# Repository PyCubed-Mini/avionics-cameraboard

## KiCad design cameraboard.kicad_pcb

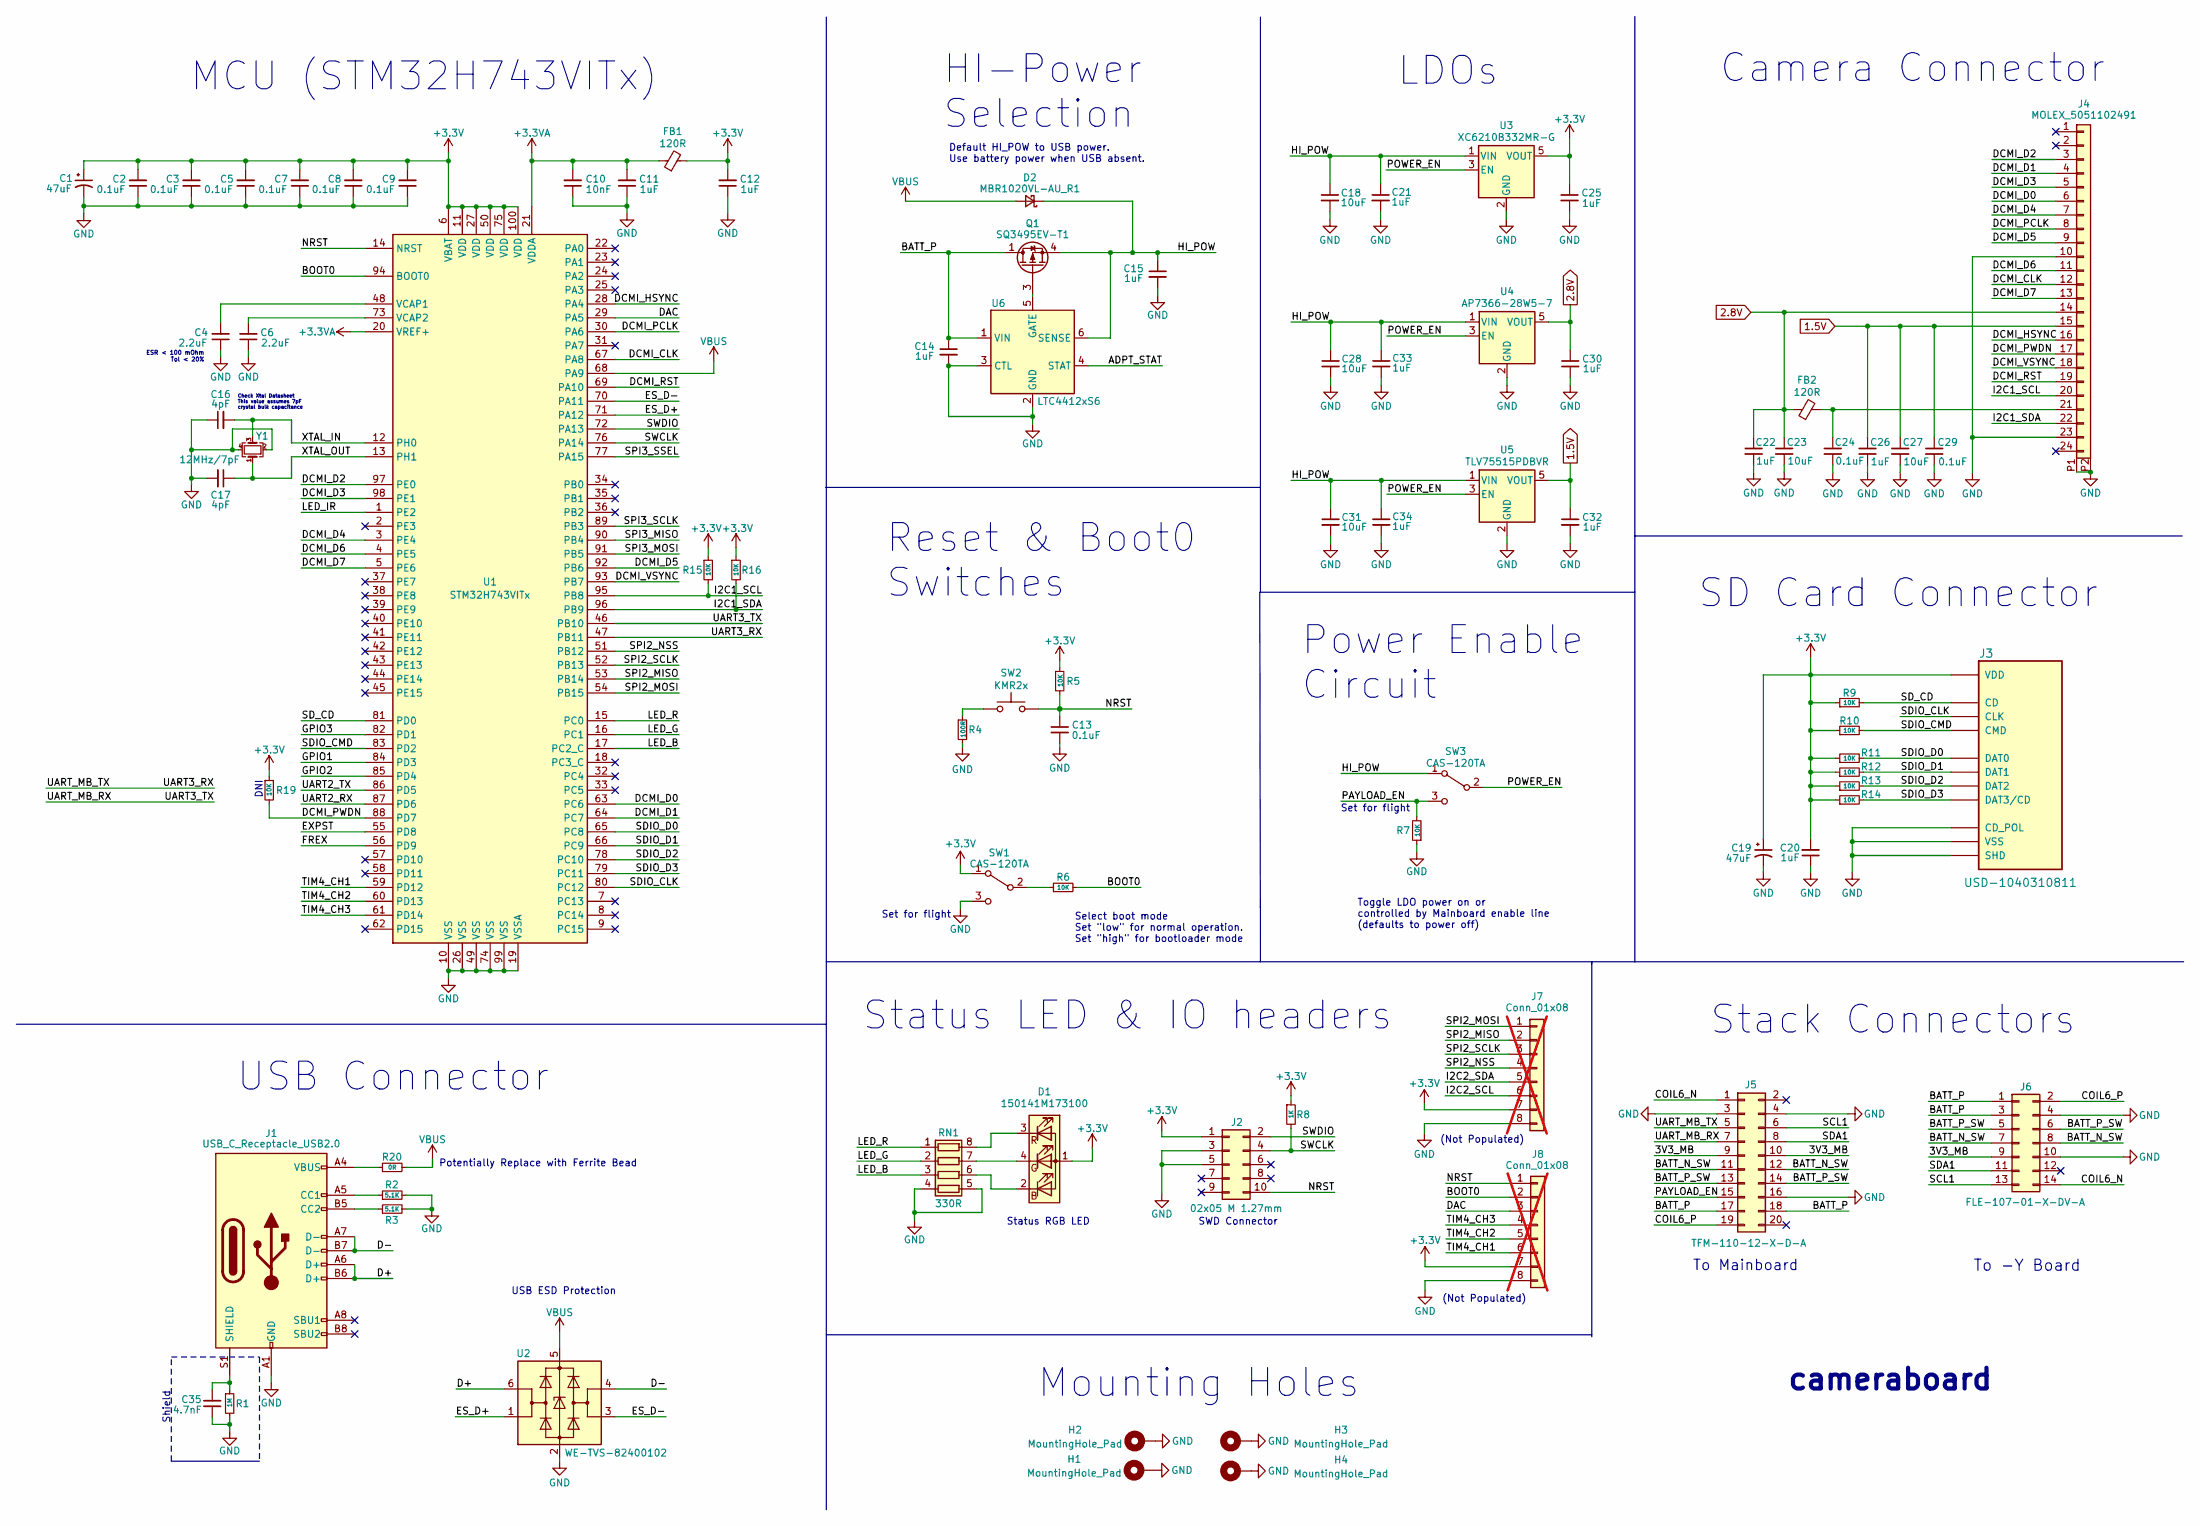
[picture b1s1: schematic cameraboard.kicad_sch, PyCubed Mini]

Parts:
C1, C19: 47uF; CP_EIA-2012-12_Kemet-R
C2, C3, C5, C7, C8, C9, C13, C24, C29: 0.1uF; C_0603_1608Metric
C4, C6: 2.2uF; C_0603_1608Metric
C10: 10nF; C_0603_1608Metric
C11, C12, C14, C15, C20, C21, C22, C25, C26, C30, C32, C33, C34: 1uF; C_0603_1608Metric
C16, C17: 4pF; C_0603_1608Metric
C18, C23, C27, C28, C31: 10uF; C_0603_1608Metric
C35: 4.7nF; C_0603_1608Metric
D1: 150141M173100; LED_RGB_Wuerth-PLCC4_3.2x2.8mm_150141M173100
D2: MBR1020VL-AU_R1; D_SOD-123F
FB1, FB2: 120R; L_0603_1608Metric
H1, H2, H3, H4: MountingHole_Pad; MountingHole
J1: USB_C_Receptacle_USB2.0; USB_C_Receptacle_HRO_TYPE-C-31-M-12
J2: 02x05 M 1.27mm; PinHeader_2x05_P1.27mm_Vertical_SMD
J3: USD-1040310811; microSD_HC_Molex_104031-0811
J4: MOLEX_5051102491
J5: TFM-110-12-X-D-A; SAMTEC_TFM-110-12-X-D-A
J6: FLE-107-01-X-DV-A; SAMTEC_FLE-107-01-X-DV-A
J7, J8: Conn_01x08; PinHeader_1x08_P2.54mm_Vertical; not fitted
Q1: SQ3495EV-T1; SOT-23-6
R1: 1M; R_0603_1608Metric
R2, R3: 5.1K; R_0603_1608Metric
R4: 100R; R_0603_1608Metric
R5, R6, R7, R9, R10, R11, R12, R13, R14, R15, R16, R19: 10K; R_0603_1608Metric
R8: 1K; R_0603_1608Metric
R20: 0R; R_0603_1608Metric
RN1: 330R; R_Array_Concave_4x0603
SW1, SW3: CAS-120TA
SW2: KMR2x; BTN_KMR2
U1: STM32H743VITx; LQFP-100_14x14mm_P0.5mm
U2: WE-TVS-82400102; SOT-23-6
U3: XC6210B332MR-G; SOT-23-5
U4: AP7366-28W5-7; SOT-23-5
U5: TLV75515PDBVR; SOT-23-5
U6: LTC4412xS6; TSOT-23-6
Y1: 12MHz/7pF; Crystal_SMD_2520-4Pin_2.5x2.0mm

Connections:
1.5V: C26.1, C27.1, C29.1, C32.1, J4.15, U5.5 (VOUT)
2.8V: C22.1, C23.1, C30.1, FB2.1, J4.14, U4.5 (VOUT)
+3.3V: C1.1, C2.2, C3.2, C5.2, C7.2, C8.2, C9.2, C12.2, C19.1, C20.2, C25.1, D1.1 (A), FB1.2, J2.1, J3.4 (VDD), J7.7, J8.7, R5.1, R8.1, R9.1, R10.1, R11.1, R12.1, R13.1, R14.1, R15.1, R16.1, R19.1, SW1.1 (A), U1.6 (VBAT), U1.11 (VDD), U1.27 (VDD), U1.50 (VDD), U1.75 (VDD), U1.100 (VDD), U3.5 (VOUT)
+3.3VA: C10.2, C11.2, FB1.1, U1.20 (VREF+), U1.21 (VDDA)
/3V3_MB: J5.9, J5.10, J6.9
/ADPT_STAT: U6.4 (STAT)
/BATT_N_SW: J5.11, J5.12, J6.7, J6.8
/BATT_P: C14.1, J5.17, J5.18, J6.1, J6.3, Q1.1 (D), Q1.2 (D), Q1.5 (D), Q1.6 (D), U6.1 (VIN)
/BATT_P_SW: J5.13, J5.14, J6.5, J6.6
/BOOT0: J8.2, R6.2, U1.94 (BOOT0)
/COIL6_N: J5.1, J6.14
/COIL6_P: J5.19, J6.2
/D+: J1.A6 (D+), J1.B6 (D+), U2.6 (I/O1)
/D-: J1.A7 (D-), J1.B7 (D-), U2.4 (I/O2)
/DAC: J8.3, U1.29 (PA5)
/DCMI_CLK: J4.12, U1.67 (PA8)
/DCMI_D0: J4.6, U1.63 (PC6)
/DCMI_D1: J4.4, U1.64 (PC7)
/DCMI_D2: J4.3, U1.97 (PE0)
/DCMI_D3: J4.5, U1.98 (PE1)
/DCMI_D4: J4.7, U1.3 (PE4)
/DCMI_D5: J4.9, U1.92 (PB6)
/DCMI_D6: J4.11, U1.4 (PE5)
/DCMI_D7: J4.13, U1.5 (PE6)
/DCMI_HSYNC: J4.16, U1.28 (PA4)
/DCMI_PCLK: J4.8, U1.30 (PA6)
/DCMI_PWDN: J4.17, R19.2, U1.88 (PD7)
/DCMI_RST: J4.19, U1.69 (PA10)
/DCMI_VSYNC: J4.18, U1.93 (PB7)
/ES_D+: U1.71 (PA12), U2.1 (I/O1)
/ES_D-: U1.70 (PA11), U2.3 (I/O2)
/EXPST: U1.55 (PD8)
/FREX: U1.56 (PD9)
/GPIO1: U1.84 (PD3)
/GPIO2: U1.85 (PD4)
/GPIO3: U1.82 (PD1)
/HI_POW: C15.1, C18.1, C21.1, C28.1, C31.1, C33.1, C34.1, D2.1 (K), Q1.4 (S), SW3.1 (A), U3.1 (VIN), U4.1 (VIN), U5.1 (VIN), U6.6 (SENSE)
/I2C1_SCL: J4.20, R15.2, U1.95 (PB8)
/I2C1_SDA: J4.22, R16.2, U1.96 (PB9)
/LED_B: RN1.3 (R3.1), U1.17 (PC2_C)
/LED_G: RN1.2 (R2.1), U1.16 (PC1)
/LED_IR: U1.1 (PE2)
/LED_R: RN1.1 (R1.1), U1.15 (PC0)
/NRST: C13.1, J2.10, J8.1, R5.2, SW2.2, U1.14 (NRST)
/PAYLOAD_EN: J5.15, R7.2, SW3.3 (C)
/POWER_EN: SW3.2 (B), U3.3 (EN), U4.3 (EN), U5.3 (EN)
/SCL1: J5.6, J6.13
/SDA1: J5.8, J6.11
/SDIO_CLK: J3.5 (CLK), U1.80 (PC12)
/SDIO_CMD: J3.3 (CMD), R10.2, U1.83 (PD2)
/SDIO_D0: J3.7 (DAT0), R11.2, U1.65 (PC8)
/SDIO_D1: J3.8 (DAT1), R12.2, U1.66 (PC9)
/SDIO_D2: J3.1 (DAT2), R13.2, U1.78 (PC10)
/SDIO_D3: J3.2 (DAT3/CD), R14.2, U1.79 (PC11)
/SD_CD: J3.10 (CD), R9.2, U1.81 (PD0)
/SPI2_MISO: J7.2, U1.53 (PB14)
/SPI2_MOSI: J7.1, U1.54 (PB15)
/SPI2_NSS: J7.4, U1.51 (PB12)
/SPI2_SCLK: J7.3, U1.52 (PB13)
/SPI3_MISO: U1.90 (PB4)
/SPI3_MOSI: U1.91 (PB5)
/SPI3_SCLK: U1.89 (PB3)
/SPI3_SSEL: U1.77 (PA15)
/SWCLK: J2.4, R8.2, U1.76 (PA14)
/SWDIO: J2.2, U1.72 (PA13)
/TIM4_CH1: J8.6, U1.59 (PD12)
/TIM4_CH2: J8.5, U1.60 (PD13)
/TIM4_CH3: J8.4, U1.61 (PD14)
/UART2_RX: U1.87 (PD6)
/UART2_TX: U1.86 (PD5)
/UART3_RX: J5.5, U1.47 (PB11)
/UART3_TX: J5.7, U1.46 (PB10)
/XTAL_IN: C16.2, U1.12 (PH0), Y1.3
/XTAL_OUT: C17.1, U1.13 (PH1), Y1.1
GND: C1.2, C2.1, C3.1, C4.1, C5.1, C6.1, C7.1, C8.1, C9.1, C10.1, C11.1, C12.1, C13.2, C14.2, C15.2, C16.1, C17.2, C18.2, C19.2, C20.1, C21.2, C22.2, C23.2, C24.2, C25.2, C26.2, C27.2, C28.2, C29.2, C30.2, C31.2, C32.2, C33.2, C34.2, C35.1, H1.1, H2.1, H3.1, H4.1, J1.A1 (GND), J1.A12 (GND), J1.B1 (GND), J1.B12 (GND), J2.3, J2.5, J3.6 (VSS), J3.9 (CD_POL), J3.11 (SHD), J4.10, J4.23, J4.P1, J4.P2, J5.3, J5.4, J5.16, J6.4, J6.10, J7.8, J8.8, R1.2, R2.2, R3.2, R4.2, R7.1, RN1.4 (R4.1), RN1.5 (R4.2), SW1.3 (C), U1.10 (VSS), U1.19 (VSSA), U1.26 (VSS), U1.49 (VSS), U1.74 (VSS), U1.99 (VSS), U2.2 (GND), U3.2 (GND), U4.2 (GND), U5.2 (GND), U6.2 (GND), U6.3 (CTL), Y1.2, Y1.4
unnamed: D1.2 (BK), RN1.6 (R3.2)
unnamed: D1.4 (GK), RN1.7 (R2.2)
unnamed: D1.3 (RK), RN1.8 (R1.2)
unnamed: J1.A5 (CC1), R2.1
unnamed: J1.B5 (CC2), R3.1
unnamed: C35.2, J1.S1 (SHIELD), R1.1
unnamed: J1.A4 (VBUS), J1.A9 (VBUS), J1.B4 (VBUS), J1.B9 (VBUS), R20.1
unnamed: C24.1, FB2.2, J4.21
unnamed: Q1.3 (G), U6.5 (GATE)
unnamed: R4.1, SW2.1
unnamed: R6.1, SW1.2 (B)
unnamed: C4.2, U1.48 (VCAP1)
unnamed: C6.2, U1.73 (VCAP2)
VBUS: D2.2 (A), R20.2, U1.68 (PA9), U2.5 (VBUS)

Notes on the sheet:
Mounting Holes
Set for flight
cameraboard
SD Card Connector
(Not Populated)
Check Xtal Datasheet This value assumes 7pF crystal bulk capacitance
Power Enable Circuit
HI-Power Selection
To Mainboard
To -Y Board
Potentially Replace with Ferrite Bead
Status LED & IO headers
DNI
MCU (STM32H743VITx)
Status RGB LED
SWD Connector
Reset & Boot0 Switches
Stack Connectors
Toggle LDO power on or controlled by Mainboard enable line (defaults to power off)
Shield
LDOs
Select boot mode Set "low" for normal operation. Set "high" for bootloader mode
USB Connector
Camera Connector
ESR < 100 mOhm Tol < 20%
Default HI_POW to USB power. Use battery power when USB absent.
USB ESD Protection

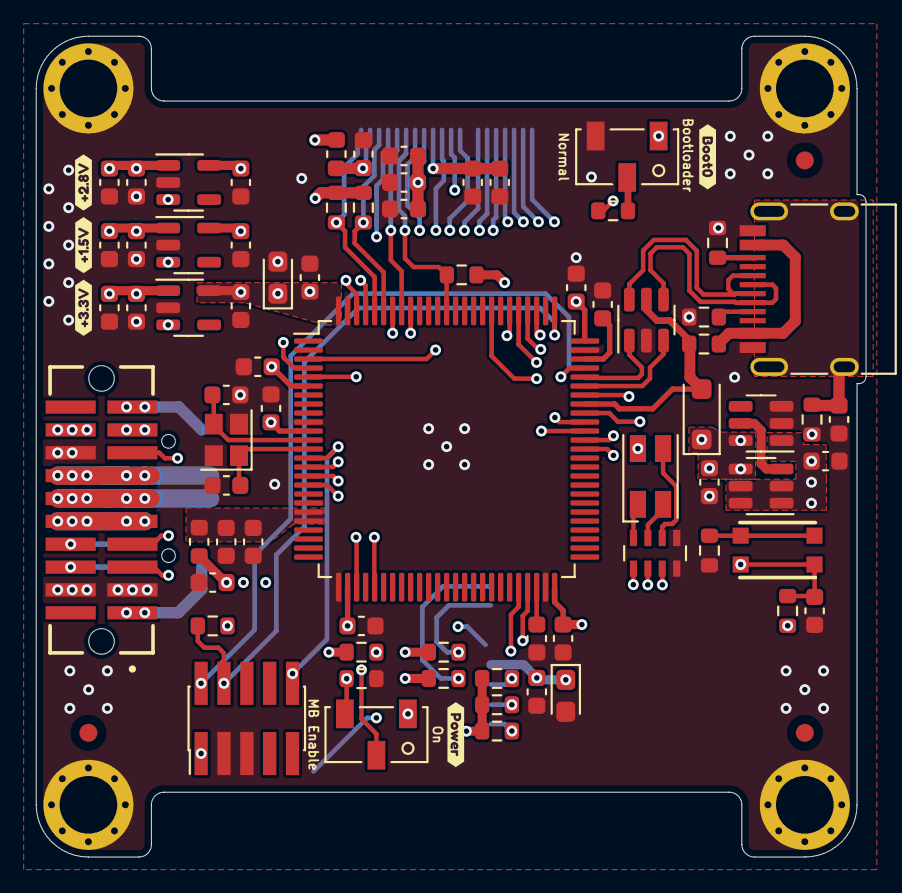
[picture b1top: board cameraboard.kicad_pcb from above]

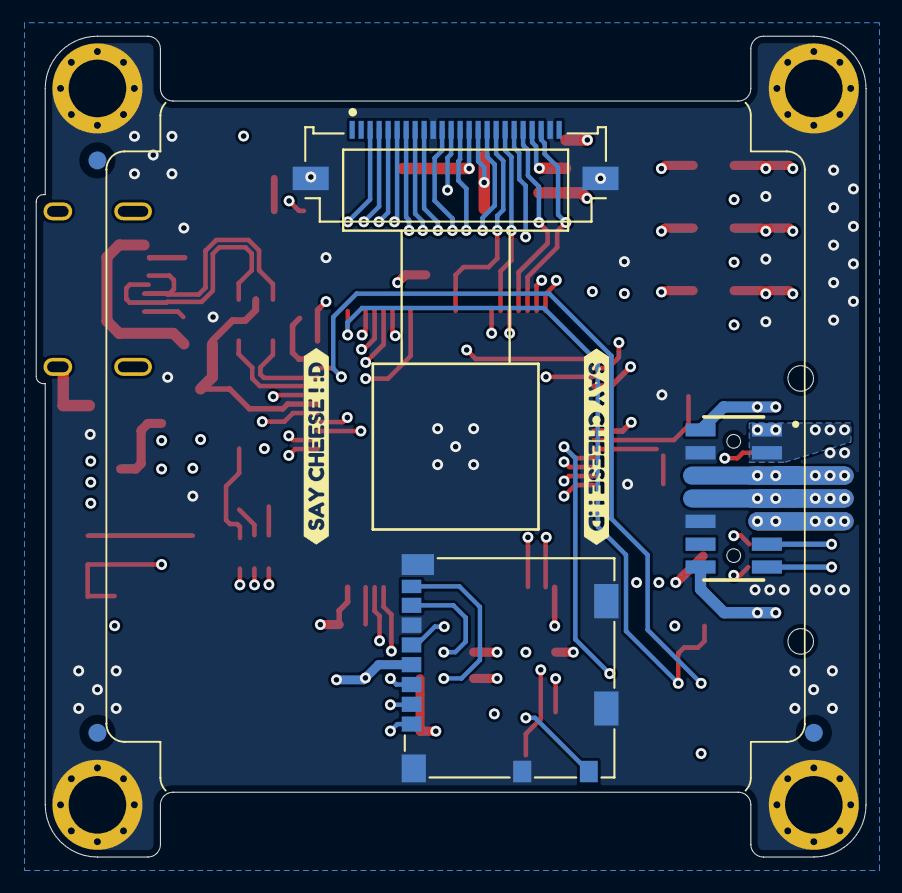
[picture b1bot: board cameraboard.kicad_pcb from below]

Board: 4 copper layers, 46.1 x 45.6 mm, 87 parts (5 on the bottom side), 68 nets.

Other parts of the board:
Ref**: Val**; pycubed_mini_half
kibuzzard-63E3EA3E: G***; kibuzzard-63E3EA3E
kibuzzard-63E3EAF3: G***; kibuzzard-63E3EAF3
kibuzzard-63E3EBF1: G***; kibuzzard-63E3EBF1
kibuzzard-63E3EC1C: G***; kibuzzard-63E3EC1C
kibuzzard-63E3EC09: G***; kibuzzard-63E3EC09
kibuzzard-63E3ED57, kibuzzard-63E3ED57#2: G***; kibuzzard-63E3ED57

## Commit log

2022-03-24 File upload
2022-03-24 camera step file
2022-03-24 black gloss
2022-03-24 Updated PCB 3d model
2022-03-25 Moved nicla model to kicad_libs, exported pcb model
2022-03-28 Added Mounting Holes on main and camera boards
2022-05-31 Changed board shape and rewired
2022-06-02 Schematic fixes and re-routing
2022-06-03 Moved stuff into place
2022-06-08 stack connectors changes
2022-06-09 VBUS -> VUSB
2022-06-09 Moved connectors as recommended
2022-06-09 Rename VBUS to VUSB and export files
2022-06-09 Added Logo, version number and date
2022-06-10 Exported Gerbers
2022-06-27 Moved Camera slightly, added bus protection
2022-06-29 moved camera connector
2022-06-29 moved connector
2022-06-29 Re-routed for new connector location
2022-06-29 Re-check board and re-export model
2022-06-30 new outline of camera board
2022-07-01 New cameraboard outline
2022-07-06 nikla -> nicla
2022-07-06 Export New Gerbers
2022-08-24 Custom spun board updates
2022-12-23 Change Stash
2023-02-08 Finished Routing
2023-02-09 Export 3D Model
2023-02-19 Simplified Enable Circuit
2023-02-22 Stash before changes
2023-02-25 Moved SWD header and power switch to prevent mechanical interference
2023-02-25 Pulled latest kicad-libs
2023-02-26 Removed gerbers from repo
2023-04-27 Rev B3/02 updates
2023-06-18 Rewired UART lines to mainboard
2023-06-19 Moved SD card connector to allow removal with rails installed
2023-06-20 PCB cleanup

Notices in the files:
parts and their libraries:
Copyright 2021 Accelerated Designs. All rights reserved.
